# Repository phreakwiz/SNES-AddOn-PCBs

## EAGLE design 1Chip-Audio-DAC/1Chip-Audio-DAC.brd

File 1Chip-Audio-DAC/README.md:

SNES 1Chip Audio DAC replacement
--------------------------------

### Purpose

This board design is suited to replace the 1Chip-SNES audio DAC, which is labeled by U6.  
This board **does not** fixes dead S-MIX, which is U10.

At the moment I don't know whether the boards fits (mechanically) into a SNES model 2 (small form factor SNES)

### Installation

- assemble the board (BOM on bottom silk screen and listed below)
- remove U6
- if you are going to recap your system, you can remove C15 and leave the footprint of C15 unpopulated  
  (it does not hurt to left C15 in place)
- connect the board to the footprint of U6. Check up for adjacent shorts afterwards.  
  (the board do not have to be isolated from bottom as it's a single layer design)
- check for connections at U6:
  - p1: R48 (bottom side mainboard) (audio out right)
  - p2: C15 + (and Vcc through board design)
  - p3: GND
  - p4: R51 (bottom side of mainboard) (audio out left)
  - p5: U2 pin 94 (LRCK)
  - p6: U2 pin 93 (DATA)
  - p7: U2 pin 92 (SCLK)
  - p8: Vcc (+5V)
- connect pad labeld by _U2:52_ with U2 pin 52 (also extension port pin 21)

### BOM

- U1: CS4338-KSZ (SOIC-8 package)
- C1: 0.1uF / 25V+ (SMD 0603 package)
- C2: 1uF /25V+ (SMD 0603 package)

### PCB

Get your PCB from [OSHPark](https://oshpark.com/shared_projects/qMppLcDq) or anywhere you like.  
To smoothen the installation, choose a substrate thickness as thin as possible.

## ENJOY!!!

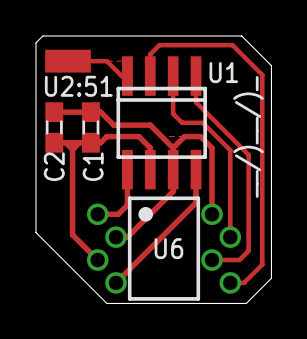
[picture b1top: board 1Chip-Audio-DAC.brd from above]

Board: 2 copper layers, 13.1 x 14.9 mm, 4 parts (0 on the bottom side), 3 nets.

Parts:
C1: 0.1u; C0603
C2: 1u; C0603
MCLK: SMD1,27-2,54
U1: CS4338-KSZ; SO-08

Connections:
AGND: C1.1, C2.1, U1.6
MCLK: MCLK.1, U1.4
VA: C1.2, C2.2, U1.7

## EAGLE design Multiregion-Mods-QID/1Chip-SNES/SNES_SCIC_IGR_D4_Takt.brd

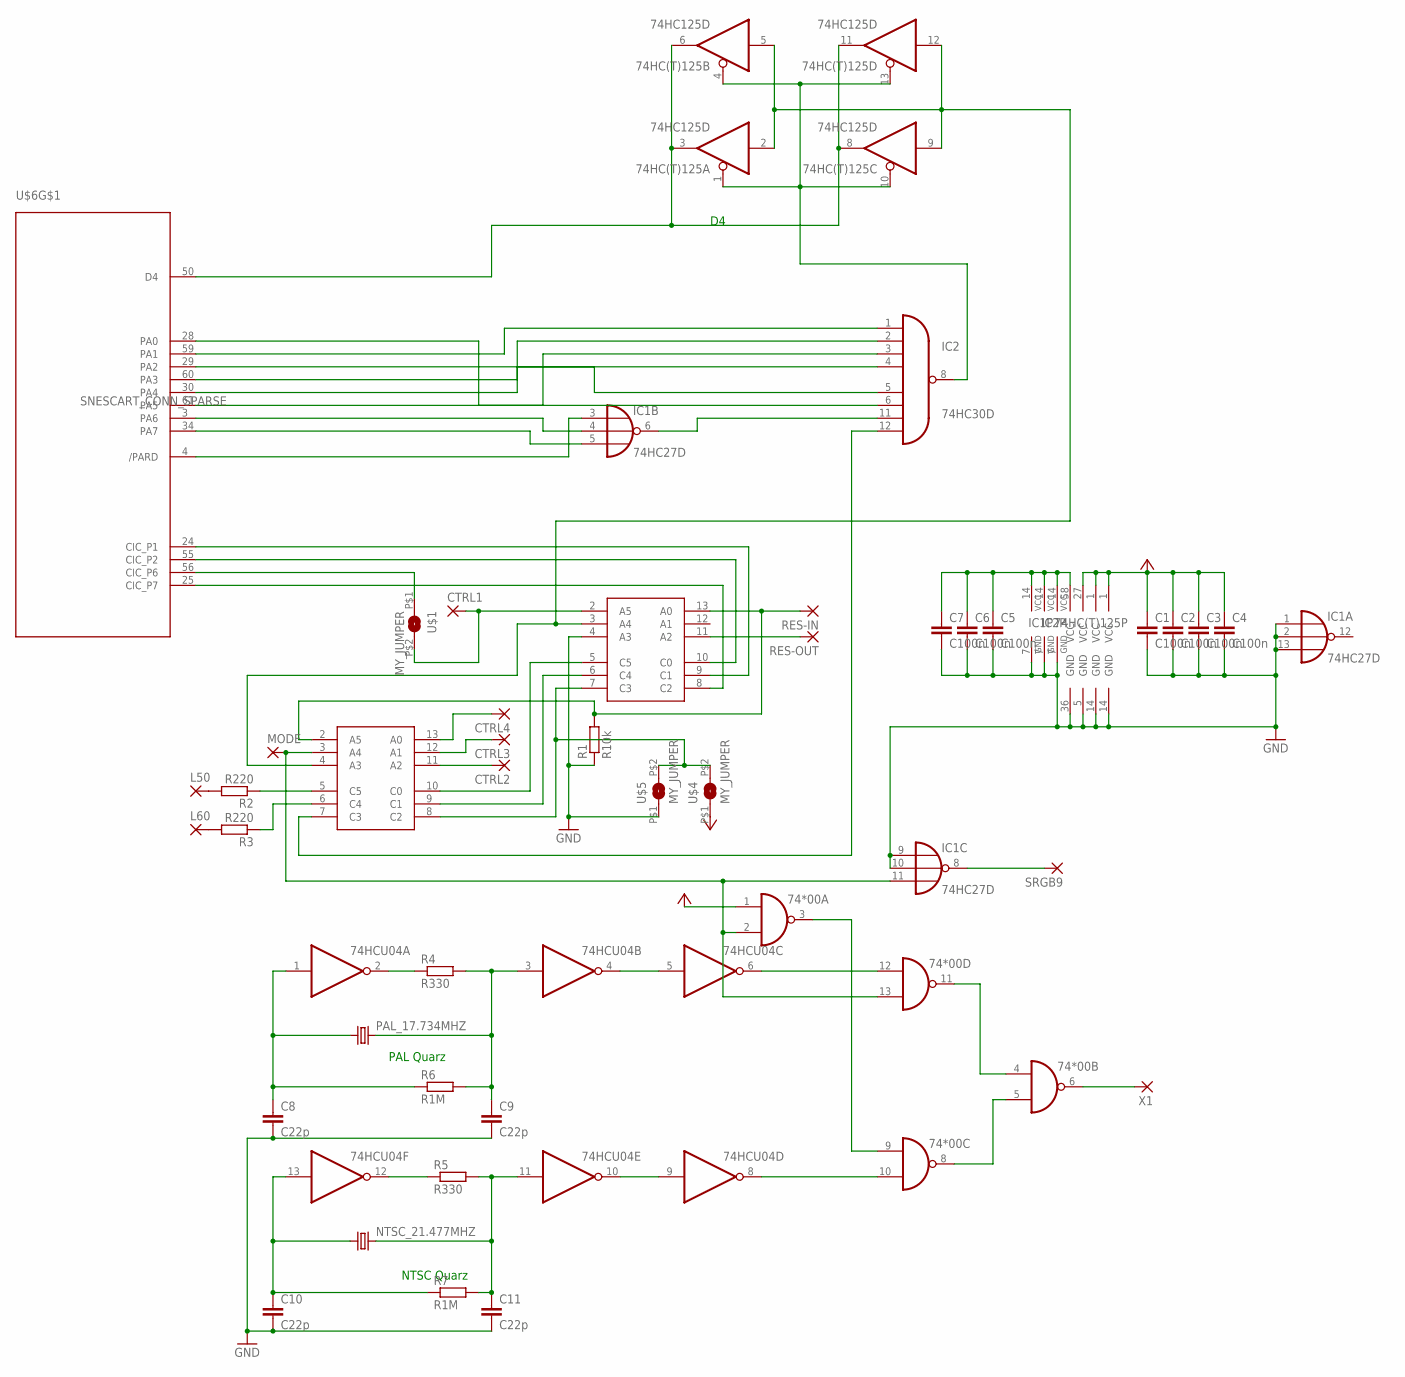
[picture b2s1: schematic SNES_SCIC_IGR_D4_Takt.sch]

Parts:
74*00: 7400D; SO14
74HC(T)125: 74HC125D; SO14
74HCU04: 74HC04D; SO14
C1, C2, C3, C4, C5, C6, C7: C100n; Z0805
C8, C9, C10, C11: C22p; Z0805
CTRL1, CTRL2, CTRL3, CTRL4: SMD2; SMD1,27-2,54
IC1: 74HC27D; SO14
IC2: 74HC30D; SO14
L50, L60: SMD2; SMD1,27-2,54
MODE: SMD2; SMD1,27-2,54
NTSC_21.477MHZ: CRYSTALHC49UP; HC49UP
PAL_17.734MHZ: CRYSTALHC49UP; HC49UP
R1: R10k; Z0805
R2, R3: R220; Z0805
R4, R5: R330; Z0805
R6, R7: R1M; Z0805
RES-IN: SMD2; SMD1,27-2,54
RES-OUT: SMD2; SMD1,27-2,54
SRGB9: SMD2; SMD1,27-2,54
U$1, U$4, U$5: MY_JUMPER; MYJUMP
U$2, U$3: PIC16F630_SIMPLE; PIC16F630
U$6: SNESCART_CONN_SPARSE
X1: SMD2; SMD1,27-2,54

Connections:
GND: 74*00.7 (GND), 74HC(T)125.7 (GND), 74HCU04.7 (GND), C1.2, C2.2, C3.2, C4.2, C5.2, C6.2, C7.2, C8.2, C9.2, C10.2, C11.2, IC1.1 (I0), IC1.2 (I1), IC1.7 (GND), IC1.9 (I0), IC1.10 (I1), IC1.13 (I2), IC2.7 (GND), R1.1, U$2.4 (A3), U$2.14 (GND), U$3.14 (GND), U$5.P$1 (1), U$6.5 (GND), U$6.36 (GND)
unnamed: IC1.8 (O), SRGB9.1
unnamed: 74HC(T)125.1 (OE), 74HC(T)125.4 (OE), 74HC(T)125.10 (OE), 74HC(T)125.13 (OE), IC2.8 (O)
unnamed: RES-OUT.1, U$2.11 (A2)
unnamed: IC2.3 (I2), U$6.61 (PA5)
unnamed: IC2.2 (I1), U$6.60 (PA3)
unnamed: IC1.3 (I0), U$6.4 (/PARD)
unnamed: IC1.4 (I1), U$6.3 (PA6)
unnamed: IC1.6 (O), IC2.11 (I6)
unnamed: IC2.6 (I5), U$6.28 (PA0)
unnamed: R1.2, RES-IN.1, U$2.13 (A0), U$3.2 (A5)
unnamed: L50.1, R2.2
unnamed: R2.1, U$3.5 (C5)
unnamed: R3.1, U$3.6 (C4)
unnamed: 74*00.2 (I1), 74*00.13 (I1), IC1.11 (I2), MODE.1, U$3.3 (A4)
unnamed: L60.1, R3.2
unnamed: IC1.5 (I2), U$6.34 (PA7)
unnamed: IC2.12 (I7), U$3.7 (C3)
unnamed: U$1.P$1 (1), U$6.56 (CIC_P6)
unnamed: U$2.5 (C5), U$3.10 (C0)
unnamed: IC2.1 (I0), U$6.59 (PA1)
unnamed: IC2.5 (I4), U$6.29 (PA2)
unnamed: IC2.4 (I3), U$6.30 (PA4)
unnamed: 74*00.12 (I0), 74HCU04.6 (O)
unnamed: 74HCU04.1 (I), C8.1, PAL_17.734MHZ.1, R6.1
unnamed: 74HCU04.3 (I), C9.1, PAL_17.734MHZ.2, R4.2, R6.2
unnamed: 74HCU04.13 (I), C10.1, NTSC_21.477MHZ.1, R7.1
unnamed: 74HCU04.11 (I), C11.1, NTSC_21.477MHZ.2, R5.2, R7.2
unnamed: 74*00.5 (I1), 74*00.8 (O)
unnamed: 74*00.4 (I0), 74*00.11 (O)
unnamed: CTRL2.1, U$3.11 (A2)
unnamed: CTRL3.1, U$3.12 (A1)
unnamed: 74*00.3 (O), 74*00.9 (I0)
unnamed: 74*00.6 (O), X1.1
unnamed: 74HCU04.2 (O), R4.1
unnamed: 74HCU04.4 (O), 74HCU04.5 (I)
unnamed: CTRL1.1, U$1.P$2 (2), U$2.2 (A5)
unnamed: 74*00.10 (I1), 74HCU04.8 (O)
unnamed: 74HC(T)125.3 (O), 74HC(T)125.6 (O), 74HC(T)125.8 (O), 74HC(T)125.11 (O), U$6.50 (D4)
unnamed: 74HCU04.9 (I), 74HCU04.10 (O)
unnamed: CTRL4.1, U$3.13 (A0)
unnamed: U$2.10 (C0), U$6.55 (CIC_P2)
unnamed: U$2.9 (C1), U$6.24 (CIC_P1)
unnamed: 74HCU04.12 (O), R5.1
unnamed: U$2.8 (C2), U$6.25 (CIC_P7)
unnamed: U$2.6 (C4), U$3.9 (C1)
unnamed: U$2.7 (C3), U$3.8 (C2), U$4.P$2 (2), U$5.P$2 (2)
UIGR: 74HC(T)125.2 (I), 74HC(T)125.5 (I), 74HC(T)125.9 (I), 74HC(T)125.12 (I), U$2.3 (A4), U$3.4 (A3)
VCC: 74*00.1 (I0), 74*00.14 (VCC), 74HCU04.14 (VCC), C1.1, C2.1, C3.1, C4.1, U$2.1 (VCC), U$3.1 (VCC), U$4.P$1 (1), U$6.27 (VCC)
VCC_2: 74HC(T)125.14 (VCC), C5.1, C6.1, C7.1, IC1.14 (VCC), IC2.14 (VCC), U$6.58 (VCC)

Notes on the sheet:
PAL Quarz
NTSC Quarz

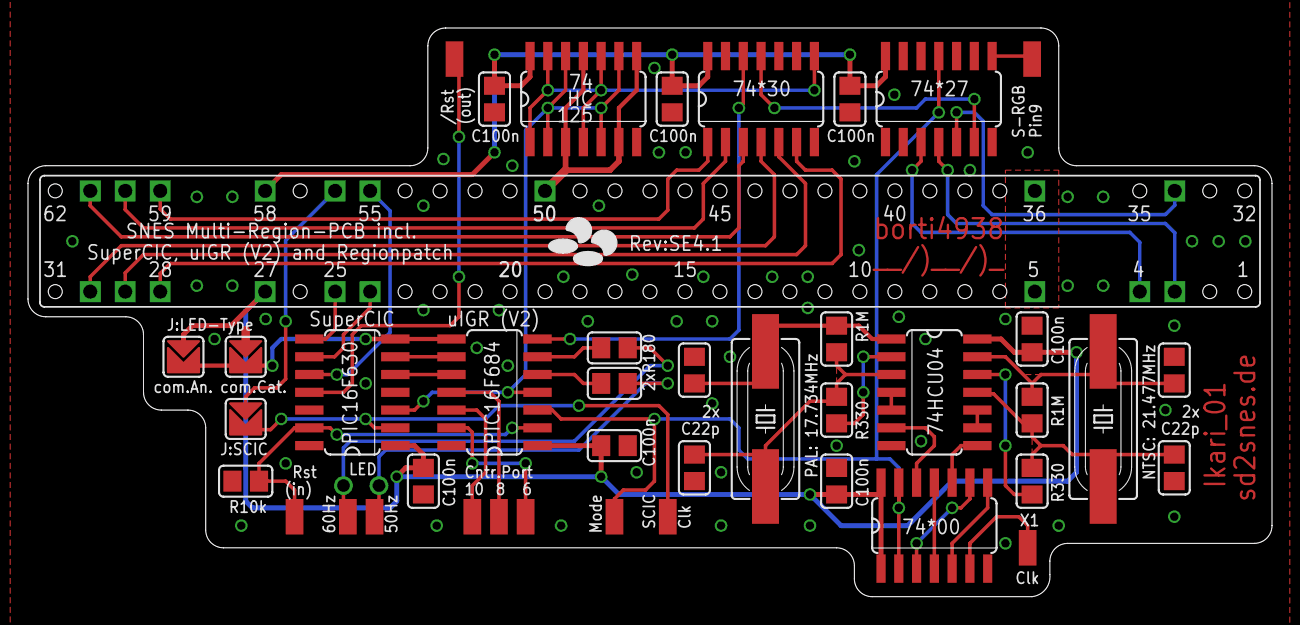
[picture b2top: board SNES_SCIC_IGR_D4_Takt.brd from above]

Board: 2 copper layers, 88.9 x 40.6 mm, 42 parts (0 on the bottom side), 50 nets.

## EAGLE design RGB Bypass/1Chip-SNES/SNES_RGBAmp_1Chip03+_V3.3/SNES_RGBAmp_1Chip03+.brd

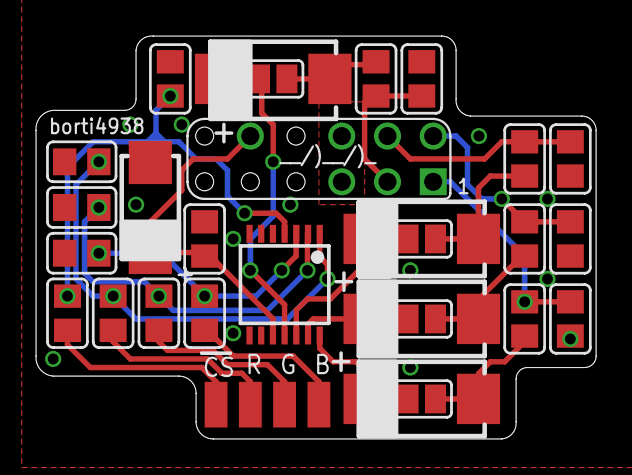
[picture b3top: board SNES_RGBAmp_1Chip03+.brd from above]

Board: 2 copper layers, 31.1 x 22.4 mm, 32 parts (0 on the bottom side), 22 nets.

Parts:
B: SMD1,27-2,54
C1: 100n; Z0805
C2: 22u; SMC_C
C3, C4, C5, C6: 330u; SMC_D
C7, C8, C9, C10: 47p; Z0805
CS: SMD1,27-2,54
G: SMD1,27-2,54
R: SMD1,27-2,54
R1, R2, R3: 75; Z0805
R4: 806; Z0805
R5, R6: 1.3k; Z0805
R7: 9.53k; Z0805
R8, R9: 8.45k; Z0805
R10: 75-421; Z0805
R11: 5.0k; Z0805
R12: 4.3k; Z0805
SJ1, SJ2, SJ3, SJ4: SJ
U$2: THS7374
U$3: SNES_MULTIAV_RGBC_ONLY

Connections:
GND: C1.2, C2.-, C7.2, C8.2, C9.2, C10.2, R7.1, R8.1, R9.1, R12.1, U$2.5, U$2.6, U$2.9, U$3.P$5, U$3.P$6
unnamed: R4.1, R7.2, U$2.1
unnamed: R5.1, R8.2, U$2.2
unnamed: C3.-, R1.1, SJ1.2
unnamed: C7.1, R1.2, U$3.P$1
unnamed: C8.1, R2.2, U$3.P$2
unnamed: C4.+, SJ2.1, U$2.13
unnamed: C5.-, R3.1, SJ3.2
unnamed: C9.1, R3.2, U$3.P$4
unnamed: R11.1, R12.2, U$2.4
unnamed: C5.+, SJ3.1, U$2.12
unnamed: C3.+, SJ1.1, U$2.14
unnamed: C4.-, R2.1, SJ2.2
unnamed: R.1, R4.2
unnamed: G.1, R5.2
unnamed: B.1, R6.2
unnamed: CS.1, R11.2
unnamed: C6.+, SJ4.1, U$2.11
unnamed: C6.-, R10.1, SJ4.2
unnamed: C10.1, R10.2, U$3.P$3
R9: R6.1, R9.2, U$2.3
VCC: C1.1, C2.+, U$2.10, U$3.P$10

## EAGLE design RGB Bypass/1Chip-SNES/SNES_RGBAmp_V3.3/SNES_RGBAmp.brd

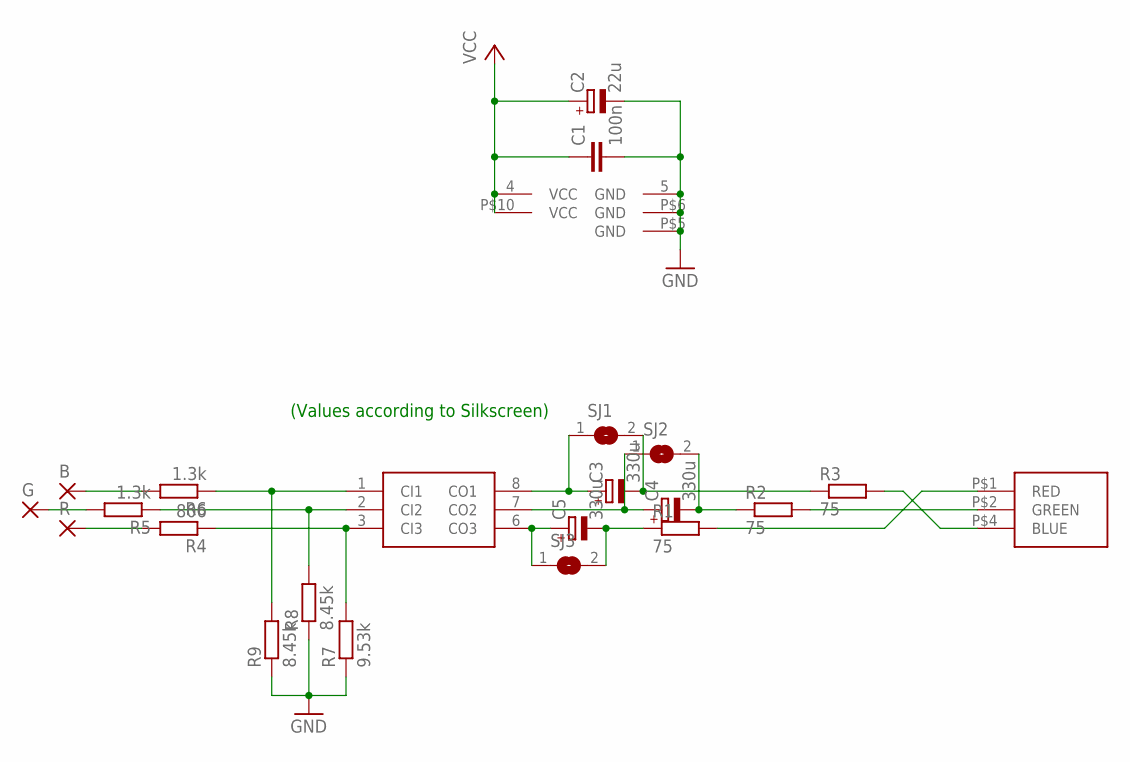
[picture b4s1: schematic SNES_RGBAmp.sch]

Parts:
B: SMD2; SMD1,27-2,54
C1: 100n; Z0805
C2: 22u; SMC_C
C3, C4, C5: 330u; SMC_D
G: SMD2; SMD1,27-2,54
R: SMD2; SMD1,27-2,54
R1, R2, R3: 75; Z0805
R4: 806; Z0805
R5, R6: 1.3k; Z0805
R7: 9.53k; Z0805
R8, R9: 8.45k; Z0805
SJ1, SJ2, SJ3: SJ
U$1: THS7314
U$2: SNES_MULTIAV_RGB_ONLY

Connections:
GND: C1.2, C2.-, R7.1, R8.1, R9.1, U$1.5 (GND), U$2.P$5 (GND), U$2.P$6 (GND)
unnamed: R6.1, R9.2, U$1.1 (CI1)
unnamed: R5.1, R8.2, U$1.2 (CI2)
unnamed: R4.1, R7.2, U$1.3 (CI3)
unnamed: C3.-, R3.1, SJ1.2
unnamed: R3.2, U$2.P$4 (BLUE)
unnamed: R2.2, U$2.P$2 (GREEN)
unnamed: C4.+, SJ2.1, U$1.7 (CO2)
unnamed: C5.-, R1.1, SJ3.2
unnamed: R1.2, U$2.P$1 (RED)
unnamed: C5.+, SJ3.1, U$1.6 (CO3)
unnamed: C3.+, SJ1.1, U$1.8 (CO1)
unnamed: C4.-, R2.1, SJ2.2
unnamed: B.1, R6.2
unnamed: G.1, R5.2
unnamed: R.1, R4.2
VCC: C1.1, C2.+, U$1.4 (VCC), U$2.P$10 (VCC)

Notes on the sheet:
(Values according to Silkscreen)

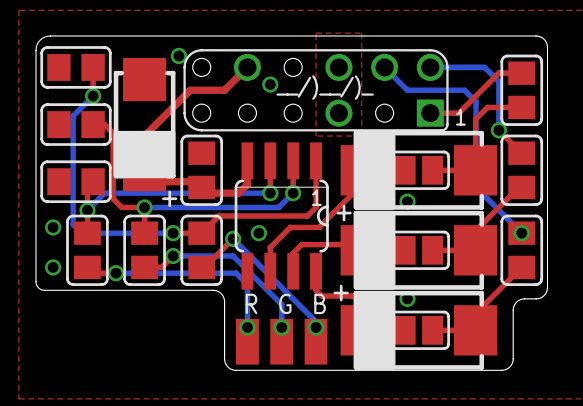
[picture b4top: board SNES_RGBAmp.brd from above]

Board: 2 copper layers, 28.4 x 18.6 mm, 22 parts (0 on the bottom side), 17 nets.

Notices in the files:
1Chip-Audio-DAC/1Chip-Audio-DAC.brd:
(c) 2018 Peter Bartmann
